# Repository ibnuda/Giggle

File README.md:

# Giggle Keyboard

You've heard houndstooth and slamd?
Just like those boards but with a middle part as arrow pad.

## What is it?

It's a board which has three parts, consisted of two alpha pads and a numpad.

## I don't get it.

Check the following pics.

As you can see, the first one is the main part of the board where the promicro
is located at.
You can put 16 keys on it and use it as an navigation pad / number pad or whatever
floats your goat.

For the 4x5 ortho or staggered one, you can use two of them, in whatever combination
you want.
But, they can only be placed as the side as you can't use the main part on the
outer part of the combination.

## I still don't get it.

Never mind.

## Oh, I get it! But why? 

The name is the clue.
I write it just for shits and giggles!

## Ok, but where's the firmware?

I haven't written it yet, mate.
But, it will surely use QMK.

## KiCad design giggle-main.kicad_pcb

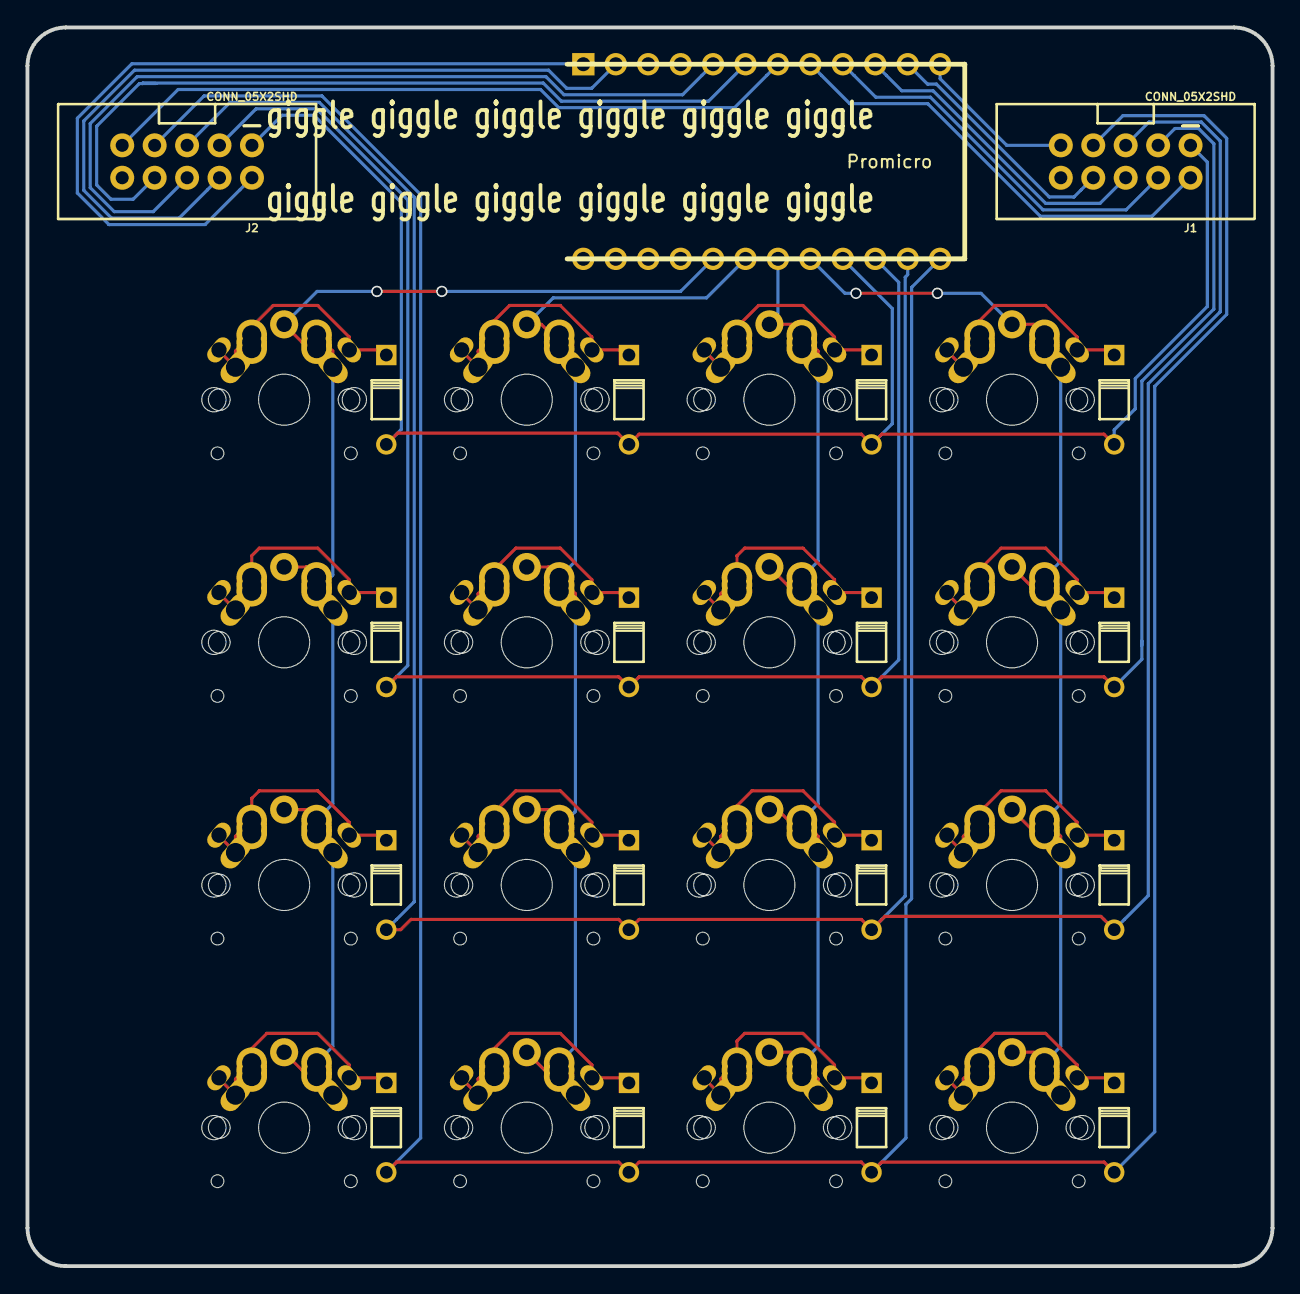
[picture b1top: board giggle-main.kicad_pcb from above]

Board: 2 copper layers, 97.5 x 97.0 mm, 35 parts (0 on the bottom side), 34 nets.

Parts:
J1, J2: CONN_05X2SHD; connector-shrouded
Promicro: PROMICRO
d0:0, d0:1, d0:2, d0:3, d1:0, d1:1, d1:2, d1:3, d2:0, d2:1, d2:2, d2:3, d3:0, d3:1, d3:2, d3:3: DIODE
sw0:0, sw0:1, sw0:2, sw0:3, sw1:0, sw1:1, sw1:2, sw1:3, sw2:0, sw2:1, sw2:2, sw2:3, sw3:0, sw3:1, sw3:2, sw3:3: SW_PUSH; MX_ALPS_PG1350_noLed

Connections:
N-col-0: J2.8, Promicro.D0
N-col-1: J2.6, Promicro.D1
N-col-2: J2.4, Promicro.RX1
N-col-3: J2.2, Promicro.TX0
N-col-4: J2.9, Promicro.D4
N-col-5: Promicro.F4, sw0:0.2, sw0:1.2, sw0:2.2, sw0:3.2
N-col-6: Promicro.F5, sw1:0.2, sw1:1.2, sw1:2.2, sw1:3.2
N-col-7: Promicro.F6, sw2:0.2, sw2:1.2, sw2:2.2, sw2:3.2
N-col-8: Promicro.F7, sw3:0.2, sw3:1.2, sw3:2.2, sw3:3.2
N-col-9: J1.8, Promicro.B4
N-col-10: J1.6, Promicro.E6
N-col-11: J1.4, Promicro.D7
N-col-12: J1.2, Promicro.C6
N-col-13: J1.9, Promicro.B5
N-diode-0: d0:0.1, sw0:0.1
N-diode-1: d0:1.1, sw0:1.1
N-diode-2: d0:2.1, sw0:2.1
N-diode-3: d0:3.1, sw0:3.1
N-diode-4: d1:0.1, sw1:0.1
N-diode-5: d1:1.1, sw1:1.1
N-diode-6: d1:2.1, sw1:2.1
N-diode-7: d1:3.1, sw1:3.1
N-diode-8: d2:0.1, sw2:0.1
N-diode-9: d2:1.1, sw2:1.1
N-diode-10: d2:2.1, sw2:2.1
N-diode-11: d2:3.1, sw2:3.1
N-diode-12: d3:0.1, sw3:0.1
N-diode-13: d3:1.1, sw3:1.1
N-diode-14: d3:2.1, sw3:2.1
N-diode-15: d3:3.1, sw3:3.1
N-row-0: J1.1, J2.1, Promicro.B1, d0:0.2, d1:0.2, d2:0.2, d3:0.2
N-row-1: J1.3, J2.3, Promicro.B3, d0:1.2, d1:1.2, d2:1.2, d3:1.2
N-row-2: J1.5, J2.5, Promicro.B2, d0:2.2, d1:2.2, d2:2.2, d3:2.2
N-row-3: J1.7, J2.7, Promicro.B6, d0:3.2, d1:3.2, d2:3.2, d3:3.2

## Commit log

2019-10-14 init commit.
2019-10-14 forgot to add readme. lmao.
2019-10-14 finished the side, i guess.
2019-10-14 placed the switches and stuff in the main, i guess.
2019-10-15 finished main side.
2019-10-15 some thing.
    1. added another connector on side part.
    2. nicer traces.
    3. added the giggle text.
2019-10-15 gerber dir.
2019-10-15 added an option to use staggered or ortho for the side part.
2019-10-17 4x4 for main.
    because why not?
2019-10-17 looks better, i guess.
2019-10-17 forgot the pcb. lmao.
2019-10-17 yes.
2019-10-29 changed switch's footprint and therefore changed the whole traces
